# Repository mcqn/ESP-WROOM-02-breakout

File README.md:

# ESP-WROOM-02-breakout

Very simple breakout PCB for the [ESP-WROOM-02](http://espressif.com/en/products/hardware/esp-wroom-02/resources) ESP8266 module.

## Programming

The esptool.py documentation, particularly from the [section on Serial Connections onwards](https://github.com/themadinventor/esptool/#serial-connections) is a useful reference when getting started with programming.

### Wiring

 * Tie the EN (chip enable) high, to 3V3
 * Connect a 3.3V serial-to-USB adapter to GND, TX and RX
 * Tie GPIO0 to GND so it enters serial bootloader mode on startup/reset
 * Pull GPIO15 to GND, preferably with a resistor
 * Pull GPIO2 to 3V3, with a resistor (e.g. 10k)

For easier operation, wire pushbuttons between GPIO0 and GND (rather than tieing it permanently) and Reset and GND.  That allows you to reset the module by pushing the button connected to the Reset line, and put it into serial bootloader mode by holding the GPIO0 pushbutton while pressing the reset button.

### Initial Checks

Once wired up, if you open a serial monitor at the rather odd baud rate of 74880 you'll see some output when the module first powers up (or after a reset).

If you see random garbage data then the baud rate is most likely wrong.  Many serial monitors (including `screen` on Linux) won't recognise the non-standard baud rate of 74880.  If you've got `pyserial` installed (e.g. if you've installed `esptool.py`) then you can use `miniterm.py`.

#### Boot Mode

The output at the odd baud rate will include a message `boot mode:(3,6)` or similar.  The numbers indicate how it's booted up.

The first digit indicates whether or not it's in programming mode.  `3` indicates normal boot, and `1` shows that it's ready for programming over serial.

### Programming With the Arduino IDE

 1. Install the latest version of the Arduino IDE - [https://www.arduino.cc/en/Main/Software](https://www.arduino.cc/en/Main/Software)
 1. Run the Arduino IDE and follow the instructions in [Sparkfun's Thing Guide](https://learn.sparkfun.com/tutorials/esp8266-thing-hookup-guide/installing-the-esp8266-arduino-addon) to install the add-on for the ESP8266.
 1. Put the module into serial bootloader mode
 1. Choose the "Generic ESP8266 Module" board in the `Tools -> Board` menu in the Arduino IDE
 1. Set the `Flash Mode` to `QIO`, `Flash Frequency` to `40MHz`, `Upload Using` to `Serial`, `CPU Frequency` to `80MHz`, `Flash Size` to `2M (1M SPIFFS)`, `Reset Method` to `ck` and `Upload Speed` to `115200`
 1. Choose the right serial port in the `Tools -> Port` menu
 1. Upload the code

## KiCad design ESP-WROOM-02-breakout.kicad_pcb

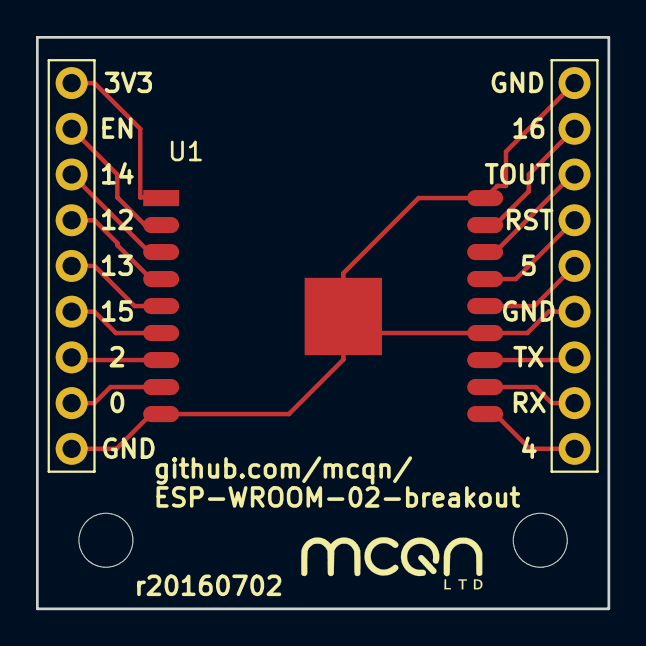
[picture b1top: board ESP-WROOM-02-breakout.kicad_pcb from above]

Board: 2 copper layers, 31.8 x 31.7 mm, 3 parts (0 on the bottom side), 16 nets.

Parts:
P1, P2: CONN_01X09; 1X09-BIG
U1: ESP-13-WROOM-02

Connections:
GND: P1.9, P2.1, P2.6, U1.9, U1.13, U1.18, U1.PAD
unnamed: P1.1, U1.1
unnamed: P1.2, U1.2
unnamed: P1.3, U1.3
unnamed: P1.4, U1.4
unnamed: P1.5, U1.5
unnamed: P1.6, U1.6
unnamed: P1.7, U1.7
unnamed: P1.8, U1.8
unnamed: P2.2, U1.17
unnamed: P2.3, U1.16
unnamed: P2.4, U1.15
unnamed: P2.5, U1.14
unnamed: P2.7, U1.12
unnamed: P2.8, U1.11
unnamed: P2.9, U1.10

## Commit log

2016-06-02 Initial version. Board submitted to Ragworm for production.
2016-07-11 Add wiring/programming instructions.
2016-07-11 Add MCQN logo to the PCB silkscreen.
2017-04-04 Add the Gerbers for easier PCB ordering
2023-04-05 Add notes about boot messages
